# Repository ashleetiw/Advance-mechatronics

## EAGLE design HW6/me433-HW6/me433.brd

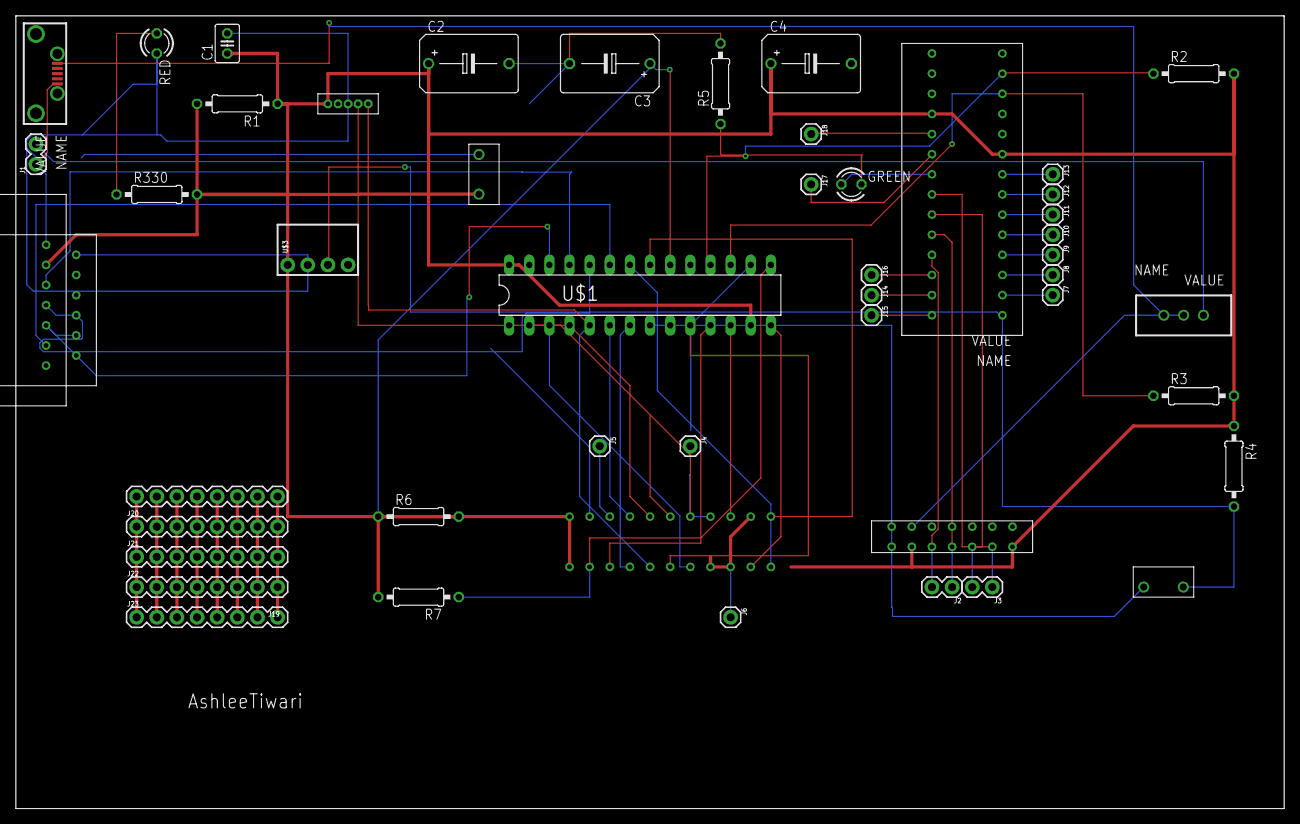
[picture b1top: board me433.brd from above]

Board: 2 copper layers, 160.0 x 100.0 mm, 49 parts (0 on the bottom side), 57 nets.

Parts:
C1: 0.1; C025-030X050
C2, C4: 0.1; B45181C
C3: 10; B45181C
GREEN: LED3MM
HBRIDGE: H_BRIDGE
J1, J2, J3: 1X02
J4, J5, J6, J7, J8, J9, J10, J11, J12, J13, J14, J15, J16, J17, J18: 1X01
J19, J20, J21, J22, J23: 1X08
R1, R2, R3, R4, R5: 10k; 0207/10
R6, R7: 4.7k; 0207/10
R330: 0207/10
RED: LED3MM
RESET: PUSH
U$1: PIC32; DIL28-3
U$2: MICROUSB
U$3: POLULU3V3; POLOLU3V3
U$4: SLIDE
U$5: FIFO_CAMERA
U$6: SNAP
U$7: USB_CON
U$8: LCD
U$10: EXPANDER
USER: PUSH

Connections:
+3V3: C1.1, C2.+, C4.+, HBRIDGE.P$2, HBRIDGE.P$7, R1.1, R1.2, R2.2, R3.2, R4.1, R6.2, R7.2, R330.2, RESET.P$1, U$1.13, U$1.28, U$3.1, U$5.P$1, U$6.P$1, U$8.P$2, U$10.P$9, U$10.P$18
+5V: U$2.1.VBUS, U$4.1
ADIR: HBRIDGE.P$6, J3.1, U$10.P$22
APWM: HBRIDGE.P$5, J3.2, U$10.P$23
B0-PGD-D4: U$1.4, U$5.P$10, U$6.P$4
B1-PGC0-D5: U$1.5, U$5.P$9, U$6.P$5
B6: R7.1, U$1.15, U$5.P$3
B7: R6.1, U$1.16, U$5.P$4
B8: R3.1, U$1.17, U$10.P$12
B9: R2.1, U$1.18, U$10.P$13
B12: U$1.23, U$8.P$6
B13: U$1.24, U$7.P$4, U$8.P$4
B14: U$1.25, U$8.P$3
B15: U$1.26, U$7.P$5, U$8.P$5
BDIR: HBRIDGE.P$4, J2.1, U$10.P$24
BPWM: HBRIDGE.P$3, J2.2, U$10.P$25
D0: U$1.2, U$5.P$14
D1: U$1.3, U$5.P$13
D3: U$1.10, U$5.P$11
D6: U$1.6, U$5.P$8
D7: U$1.7, U$5.P$7
GND: C1.2, C2.-, C3.-, C4.-, HBRIDGE.P$1, HBRIDGE.P$8, J1.1, R5.2, RED.K, RESET.P$2, U$1.8, U$1.19, U$1.27, U$2.5.GND, U$3.2, U$5.P$2, U$6.P$3, U$7.P$1, U$8.P$1, U$10.P$10, U$10.P$15, U$10.P$16, U$10.P$17, USER.P$2
unnamed: C3.+, U$1.20
unnamed: R330.1, RED.A
unnamed: GREEN.A, U$10.P$21
unnamed: R4.2, U$10.P$1, USER.P$1
unnamed: GREEN.K, R5.1
unnamed: J6.1, U$5.P$17
unnamed: J4.1, U$5.P$16
unnamed: J7.1, U$10.P$2
unnamed: J8.1, U$10.P$3
unnamed: J9.1, U$10.P$4
unnamed: J10.1, U$10.P$5
unnamed: J11.1, U$10.P$6
unnamed: J12.1, U$10.P$7
unnamed: J13.1, U$10.P$8
unnamed: J14.1, U$10.P$27
unnamed: J15.1, U$10.P$28
unnamed: J16.1, U$10.P$26
unnamed: J17.1, U$10.P$20
unnamed: J18.1, U$10.P$19
unnamed: J19.8, J20.8, J21.8, J22.8, J23.8
unnamed: J19.7, J20.7, J21.7, J22.7, J23.7
unnamed: J19.6, J20.6, J21.6, J22.6, J23.6
unnamed: J19.5, J20.5, J21.5, J22.5, J23.5
unnamed: J19.4, J20.4, J21.4, J22.4, J23.4
unnamed: J19.3, J20.3, J21.3, J22.3, J23.3
unnamed: J19.2, J20.2, J21.2, J22.2, J23.2
unnamed: J19.1, J20.1, J21.1, J22.1, J23.1
RCK: U$1.12, U$5.P$18
RRST: U$1.21, U$5.P$22
S$2: U$5.P$15, U$5.P$20
V+: J1.2, U$4.3
VIN: HBRIDGE.P$9, U$3.3, U$4.2
VSY: U$1.11, U$5.P$5
WR: U$1.14, U$5.P$19
WRST: U$1.22, U$5.P$21

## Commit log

2021-06-09 hw code uploaded
2021-06-09 added hw11 code
2021-06-09 added videos and images
2021-06-10 added inside a folder
2021-06-12 push HW6
2021-06-13 hw16 added
2021-06-13 pushed new one
2021-06-13 added recent one
